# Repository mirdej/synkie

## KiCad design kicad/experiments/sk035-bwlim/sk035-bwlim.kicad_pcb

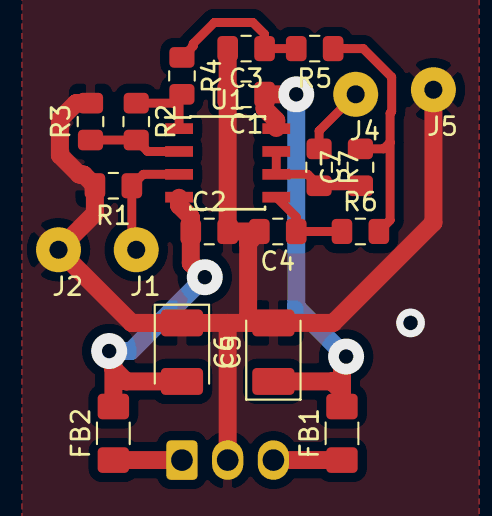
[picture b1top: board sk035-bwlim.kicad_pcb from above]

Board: 2 copper layers, 22 parts (1 on the bottom side), 13 nets.

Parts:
C1, C2: 100n; C_0805_2012Metric_Pad1.15x1.40mm_HandSolder
C3, C7: 47p; C_0805_2012Metric_Pad1.15x1.40mm_HandSolder
C4: 10p; C_0805_2012Metric_Pad1.15x1.40mm_HandSolder
C5, C6: 10u; CP_EIA-3528-21_Kemet-B_Pad1.50x2.35mm_HandSolder
FB1, FB2: Ferrite_Bead; L_1206_3216Metric_Pad1.42x1.75mm_HandSolder
J1, J2, J4, J5: Conn_01x01; Solderpad_1mm
J3: Conn_01x03; Molex_KK-254_AE-6410-03A_1x03_P2.54mm_Vertical
R1: 75; C_0805_2012Metric_Pad1.15x1.40mm_HandSolder
R2, R3: 220; R_0805_2012Metric_Pad1.15x1.40mm_HandSolder
R4, R6: 330; R_0805_2012Metric_Pad1.15x1.40mm_HandSolder
R5: 1k; R_0805_2012Metric_Pad1.15x1.40mm_HandSolder
R7: 75; R_0805_2012Metric_Pad1.15x1.40mm_HandSolder
U1: Opamp_Dual_Generic; SOIC-8_3.9x4.9mm_P1.27mm

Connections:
+5V: C1.1, C5.1, FB1.2, U1.8
-5V: C2.1, C6.2, FB2.2, U1.4
GND: C1.2, C2.2, C3.2, C4.2, C5.2, C6.1, J2.1, J3.2, J5.1, R1.2, R3.2
unnamed: C3.1, R4.1, R5.2
unnamed: C4.1, R6.1, U1.5
unnamed: C7.1, R7.2, U1.6, U1.7
unnamed: C7.2, R5.1, R6.2
unnamed: FB1.1, J3.3
unnamed: FB2.1, J3.1
unnamed: J1.1, R1.1, U1.3
unnamed: J4.1, R7.1
unnamed: R2.1, R4.2, U1.1
unnamed: R2.2, R3.1, U1.2

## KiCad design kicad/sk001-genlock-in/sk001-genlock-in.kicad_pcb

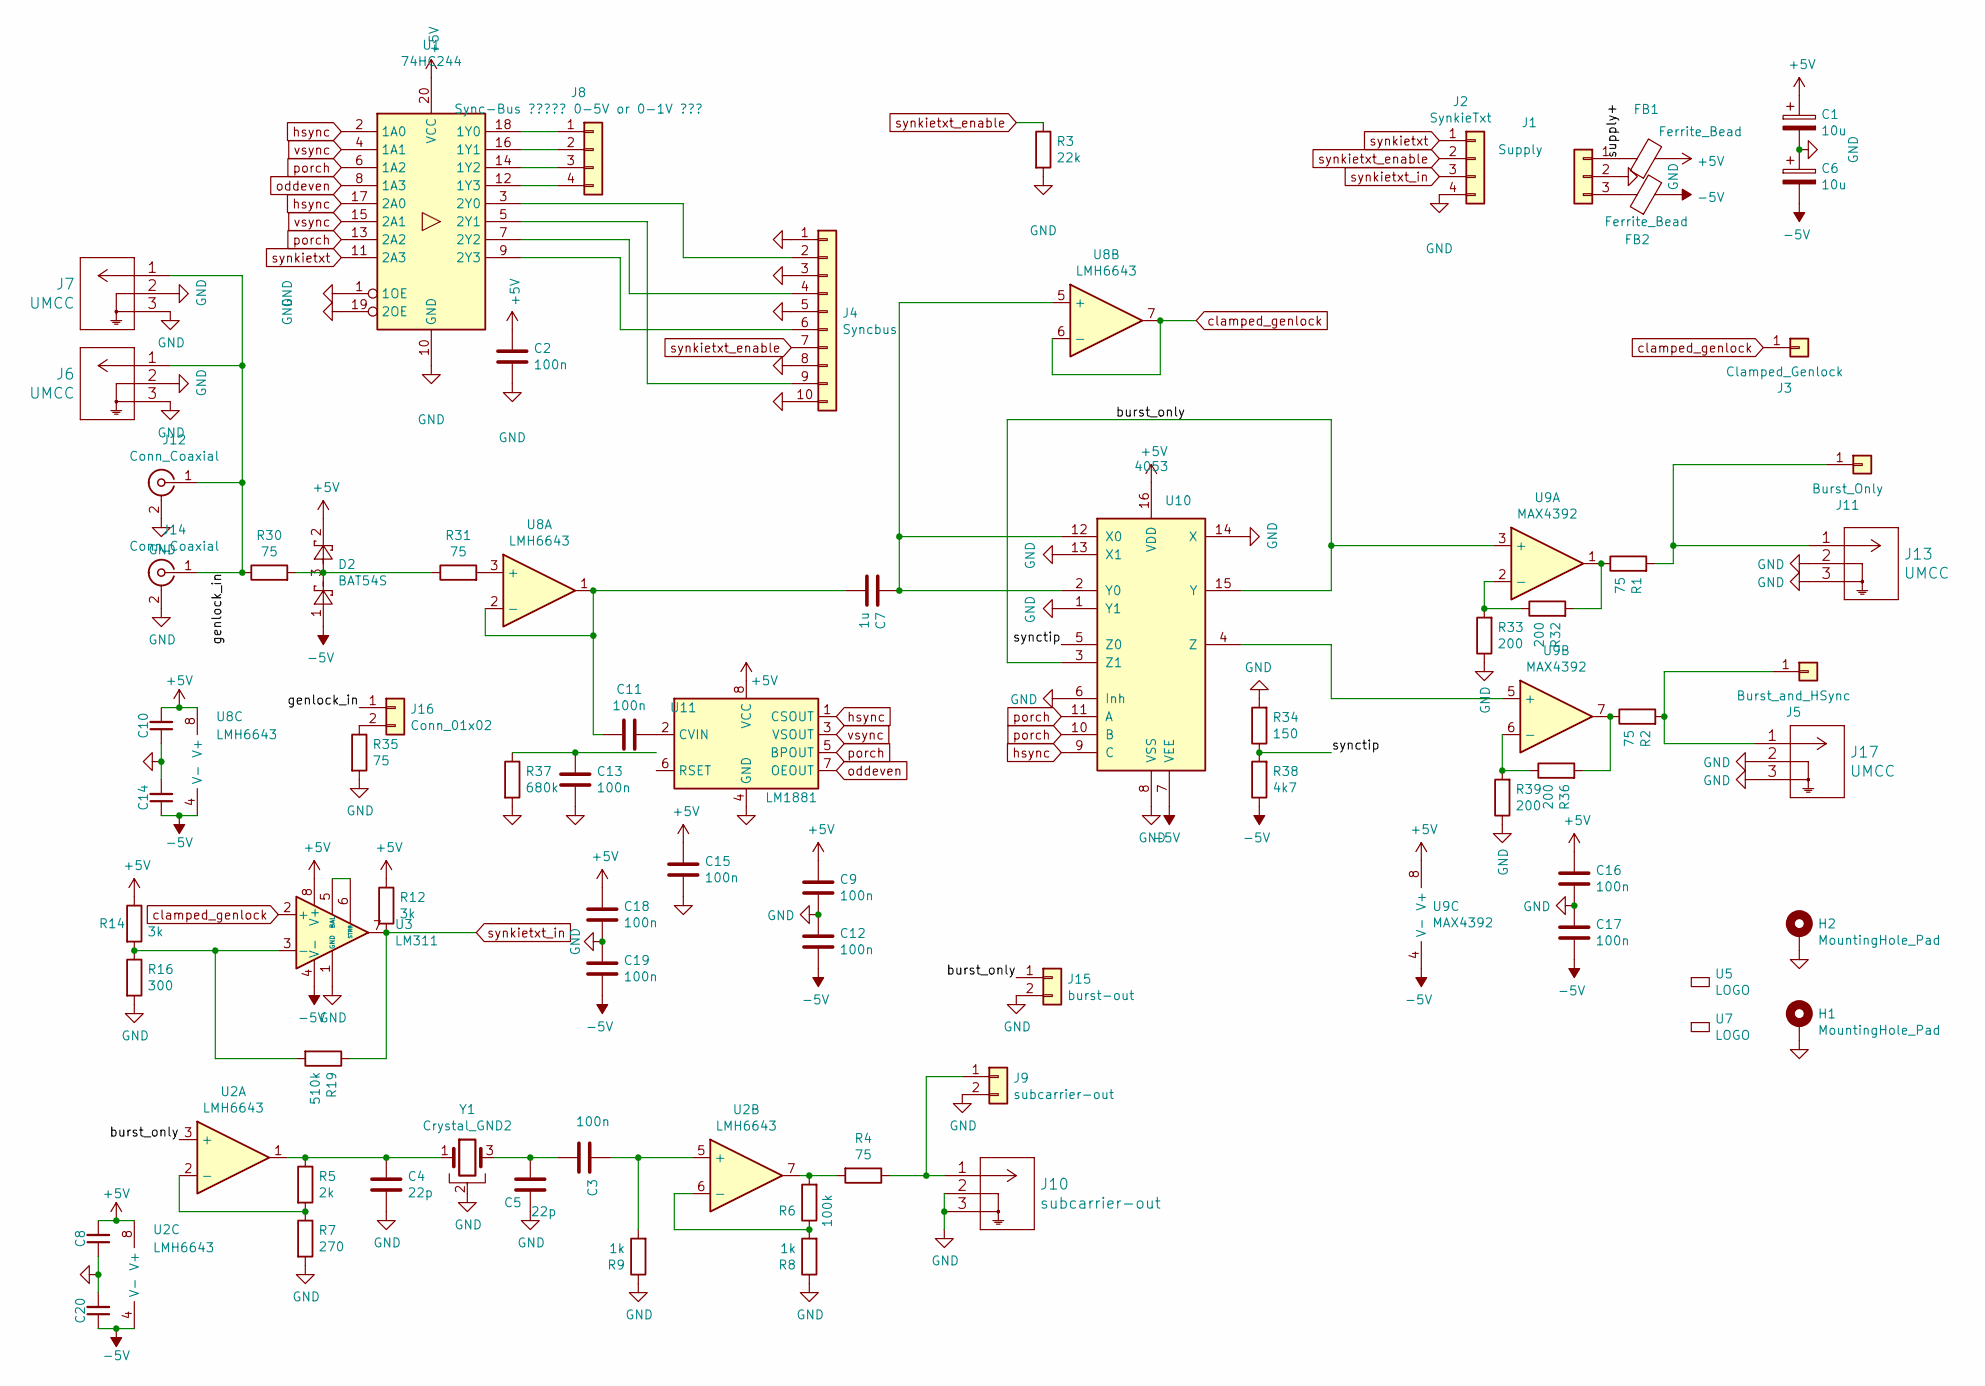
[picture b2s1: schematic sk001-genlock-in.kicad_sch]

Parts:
C1, C6: 10u; CP_EIA-3528-21_Kemet-B_Pad1.50x2.35mm_HandSolder
C2: 100n; R_0603_1608Metric_Pad1.05x0.95mm_HandSolder
C3, C8, C9, C10, C11, C12, C13, C14, C15, C16, C17, C18, C19, C20: 100n; C_0603_1608Metric_Pad1.05x0.95mm_HandSolder
C4, C5: 22p; C_0805_2012Metric_Pad1.15x1.40mm_HandSolder
C7: 1u; C_1206_3216Metric_Pad1.42x1.75mm_HandSolder
D2: BAT54S; SOT-23
FB1, FB2: Ferrite_Bead; L_0805_2012Metric_Pad1.15x1.40mm_HandSolder
H1, H2: MountingHole_Pad; MountingHole_2.7mm_M2.5_ISO7380_Pad
J1: Supply; Molex_KK-254_AE-6410-03A_1x03_P2.54mm_Vertical
J2: SynkieTxt; Molex_KK-254_AE-6410-04A_1x04_P2.54mm_Vertical
J3: Clamped_Genlock; Solderpad_1mm
J4: Syncbus; IDC-Header_2x05_P2.54mm_Vertical
J5: Burst_and_HSync; Solderpad_1mm
J6, J7, J13, J17: UMCC; TE_UMCC_2337019-1
J8: Sync-Bus ????? 0-5V or 0-1V ???; Molex_KK-254_AE-6410-04A_1x04_P2.54mm_Vertical
J9: subcarrier-out; Molex_KK-254_AE-6410-02A_1x02_P2.54mm_Vertical
J10: subcarrier-out; TE_UMCC_2337019-1
J11: Burst_Only; Solderpad_1mm
J12, J14: Conn_Coaxial; BNC_MOLEX_0731000080_Horizontal
J15: burst-out; Molex_KK-254_AE-6410-02A_1x02_P2.54mm_Vertical
J16: Conn_01x02; PinHeader_1x02_P2.54mm_Vertical
R1, R2, R4, R30, R31, R35: 75; R_0805_2012Metric_Pad1.15x1.40mm_HandSolder
R3: 22k; R_0805_2012Metric_Pad1.15x1.40mm_HandSolder
R5: 2k; R_0805_2012Metric_Pad1.15x1.40mm_HandSolder
R6: 100k; R_0805_2012Metric_Pad1.15x1.40mm_HandSolder
R7: 270; R_0805_2012Metric_Pad1.15x1.40mm_HandSolder
R8, R9: 1k; R_0805_2012Metric_Pad1.15x1.40mm_HandSolder
R12, R14: 3k; R_0805_2012Metric_Pad1.15x1.40mm_HandSolder
R16: 300; R_0805_2012Metric_Pad1.15x1.40mm_HandSolder
R19: 510k; R_0805_2012Metric_Pad1.15x1.40mm_HandSolder
R32, R33, R36, R39: 200; R_0805_2012Metric_Pad1.15x1.40mm_HandSolder
R34: 150; R_0805_2012Metric_Pad1.15x1.40mm_HandSolder
R37: 680k; R_0805_2012Metric_Pad1.15x1.40mm_HandSolder
R38: 4k7; R_0805_2012Metric_Pad1.15x1.40mm_HandSolder
U1: 74HC244; SO-20_12.8x7.5mm_P1.27mm
U2, U8: LMH6643; SOIC-8_3.9x4.9mm_P1.27mm
U3: LM311; SOIC-8_3.9x4.9mm_P1.27mm
U5: LOGO; logo_anyma
U7: LOGO; OSHW-Logo2_7.3x6mm_SilkScreen
U9: MAX4392; SOIC-8_3.9x4.9mm_P1.27mm
U10: 4053; SOIC-16_3.9x9.9mm_P1.27mm
U11: LM1881; SOIC-8_3.9x4.9mm_P1.27mm
Y1: Crystal_GND2; Crystal_SMD_HC49-SD_HandSoldering_3pin

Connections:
+5V: C1.1, C2.1, C8.2, C9.1, C10.2, C15.1, C16.1, C18.1, D2.2, FB1.2, R12.1, R14.1, U1.20 (VCC), U2.8 (V+), U3.8 (V+), U8.8 (V+), U9.8 (V+), U10.16 (VDD), U11.8 (VCC)
-5V: C6.2, C12.2, C14.1, C17.2, C19.2, C20.1, D2.1, FB2.2, R38.1, U2.4 (V-), U3.4 (V-), U8.4 (V-), U9.4 (V-), U10.7 (VEE)
/burst_only: J15.1, U2.3 (+), U9.3 (+), U10.3 (Z1), U10.15 (Y)
/genlock_in: J6.1, J7.1, J12.1 (In), J14.1 (In), J16.1, R30.1
/supply+: FB1.1, J1.1
/synctip: R34.1, R38.2, U10.5 (Z0)
GND: C1.2, C2.2, C4.2, C5.2, C6.1, C8.1, C9.2, C10.1, C12.1, C13.2, C14.2, C15.2, C16.2, C17.1, C18.2, C19.1, C20.2, H1.1, H2.1, J1.2, J2.4, J4.1, J4.3, J4.5, J4.8, J4.10, J6.2, J6.3, J7.2, J7.3, J9.2, J10.2, J10.3, J12.2 (Ext), J13.2, J13.3, J14.2 (Ext), J15.2, J17.2, J17.3, R3.2, R7.2, R8.1, R9.1, R16.2, R33.1, R34.2, R35.2, R37.2, R39.1, U1.1 (1OE), U1.10 (GND), U1.19 (2OE), U3.1 (GND), U10.1 (Y1), U10.6 (Inh), U10.8 (VSS), U10.13 (X1), U10.14 (X), U11.4 (GND), Y1.2
unnamed: C3.1, R9.2, U2.5 (+)
unnamed: C3.2, C5.1, Y1.3
unnamed: C4.1, R5.1, U2.1, Y1.1
unnamed: C7.1, U8.5 (+), U10.2 (Y0), U10.12 (X0)
unnamed: C11.1, U11.2 (CVIN)
unnamed: C7.2, C11.2, U8.1, U8.2 (-)
unnamed: D2.3, R30.2, R31.1
unnamed: FB2.1, J1.3
unnamed: J4.2, U1.3 (2Y0)
unnamed: J4.4, U1.7 (2Y2)
unnamed: J4.6, U1.9 (2Y3)
unnamed: J4.9, U1.5 (2Y1)
unnamed: J8.1, U1.18 (1Y0)
unnamed: J8.2, U1.16 (1Y1)
unnamed: J8.3, U1.14 (1Y2)
unnamed: J8.4, U1.12 (1Y3)
unnamed: J9.1, J10.1, R4.1
unnamed: J11.1, J13.1, R1.2
unnamed: J16.2, R35.1
unnamed: J5.1, J17.1, R2.2
unnamed: R1.1, R32.2, U9.1
unnamed: R2.1, R36.2, U9.7
unnamed: R4.2, R6.2, U2.7
unnamed: R5.2, R7.1, U2.2 (-)
unnamed: R6.1, R8.2, U2.6 (-)
unnamed: R14.2, R16.1, R19.2, U3.3 (-)
unnamed: R31.2, U8.3 (+)
unnamed: R32.1, R33.2, U9.2 (-)
unnamed: R36.1, R39.2, U9.6 (-)
unnamed: U3.5 (BAL), U3.6 (STRB)
unnamed: U9.5 (+), U10.4 (Z)
clamped_genlock: J3.1, U3.2 (+), U8.6 (-), U8.7
hsync: U1.2 (1A0), U1.17 (2A0), U10.9 (C), U11.1 (CSOUT)
oddeven: U1.8 (1A3), U11.7 (OEOUT)
porch: U1.6 (1A2), U1.13 (2A2), U10.10 (B), U10.11 (A), U11.5 (BPOUT)
synkietxt: J2.1, U1.11 (2A3)
synkietxt_enable: J2.2, J4.7, R3.1
synkietxt_in: J2.3, R12.2, R19.1, U3.7
vsync: U1.4 (1A1), U1.15 (2A1), U11.3 (VSOUT)

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
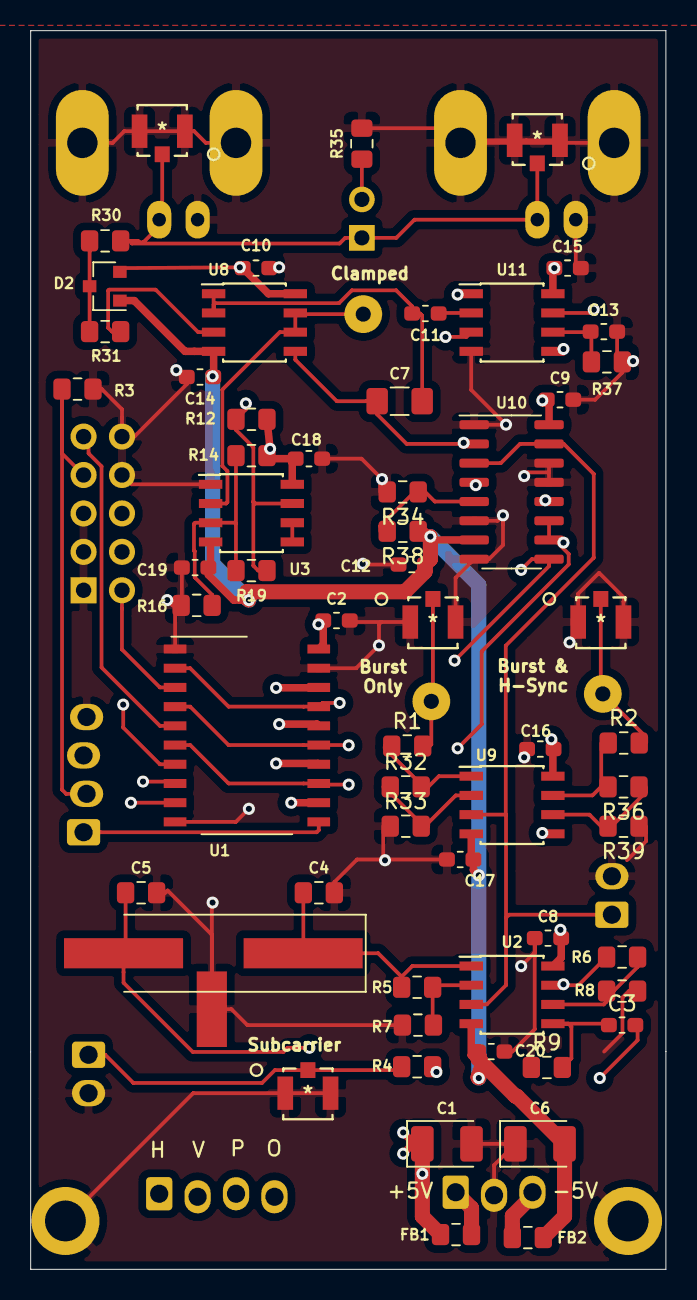
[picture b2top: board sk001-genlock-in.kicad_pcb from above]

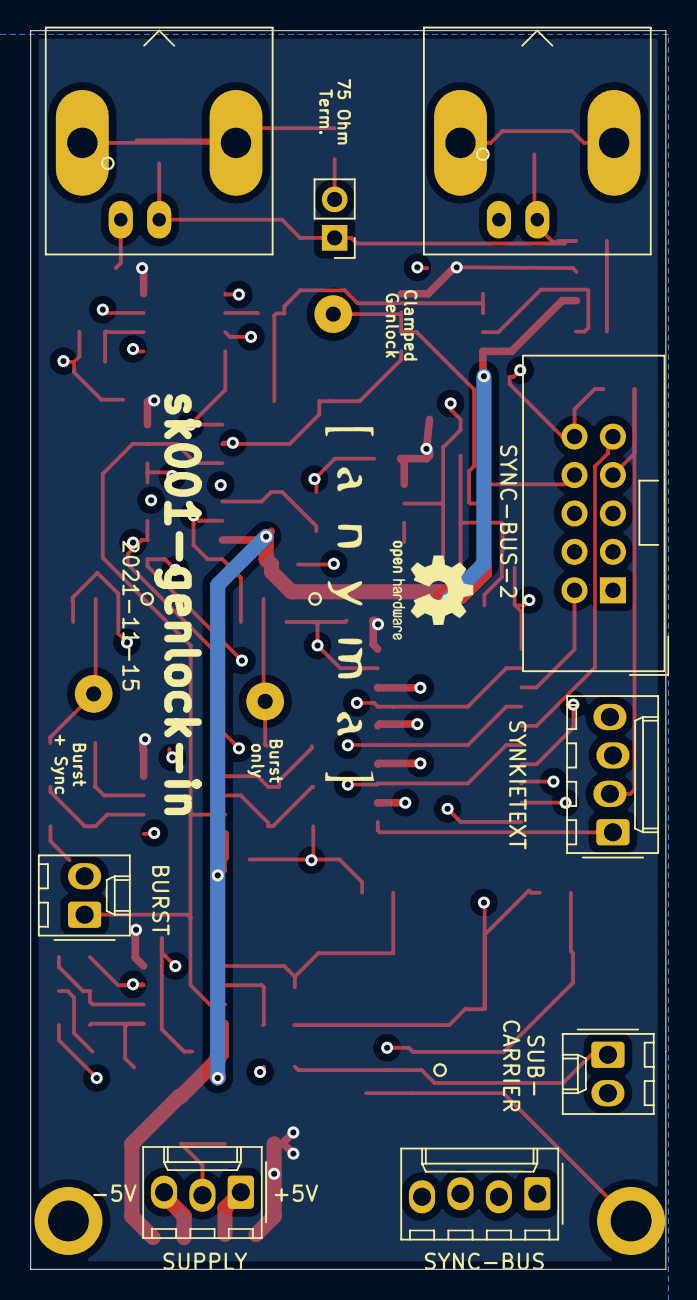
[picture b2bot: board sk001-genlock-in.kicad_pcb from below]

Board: 4 copper layers, 42.0 x 81.9 mm, 75 parts (11 on the bottom side), 47 nets.

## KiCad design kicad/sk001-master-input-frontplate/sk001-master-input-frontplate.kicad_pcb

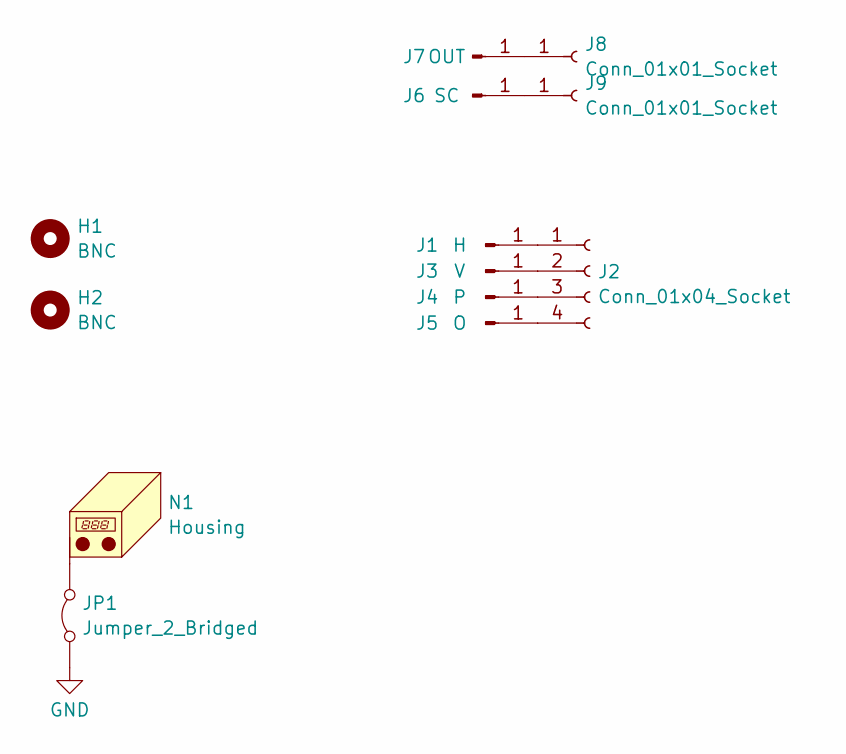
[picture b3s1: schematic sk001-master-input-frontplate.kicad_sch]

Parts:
H1, H2: BNC; MolexBNCFrontpanel
J1: H; Banana2mm-Löthülse
J2: Conn_01x04_Socket; smd-4pin
J3: V; Banana2mm-Löthülse
J4: P; Banana2mm-Löthülse
J5: O; Banana2mm-Löthülse
J6: SC; Banana2mm-Löthülse
J7: OUT; Banana2mm-Löthülse
J8, J9: Conn_01x01_Socket; smd-1pin
JP1: Jumper_2_Bridged; SolderJumper-2_P1.3mm_Bridged2Bar_Pad1.0x1.5mm
N1: Housing; Frontplate_20mm

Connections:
GND: JP1.1 (A)
unnamed: J1.1, J2.1
unnamed: J2.2, J3.1
unnamed: J2.3, J4.1
unnamed: J2.4, J5.1
unnamed: J6.1, J9.1
unnamed: J7.1, J8.1
unnamed: JP1.2 (B), N1.1 (PAD)

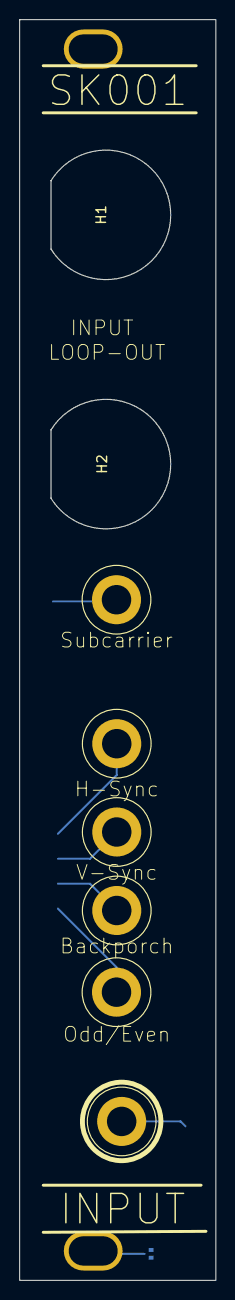
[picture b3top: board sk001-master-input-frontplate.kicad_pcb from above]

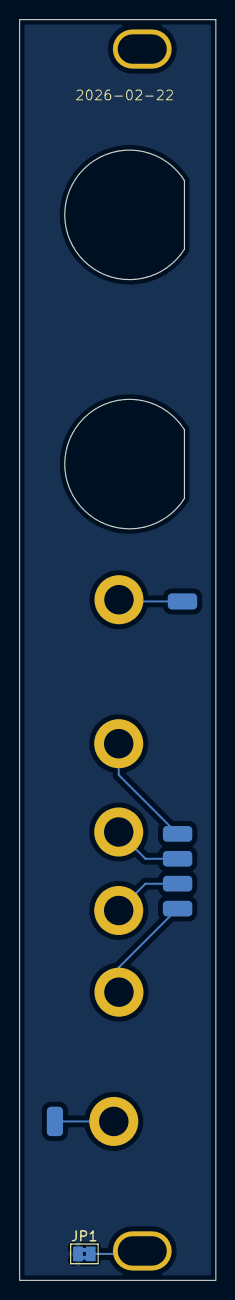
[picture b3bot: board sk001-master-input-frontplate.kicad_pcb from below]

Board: 2 copper layers, 20.0 x 128.5 mm, 13 parts (4 on the bottom side), 7 nets.

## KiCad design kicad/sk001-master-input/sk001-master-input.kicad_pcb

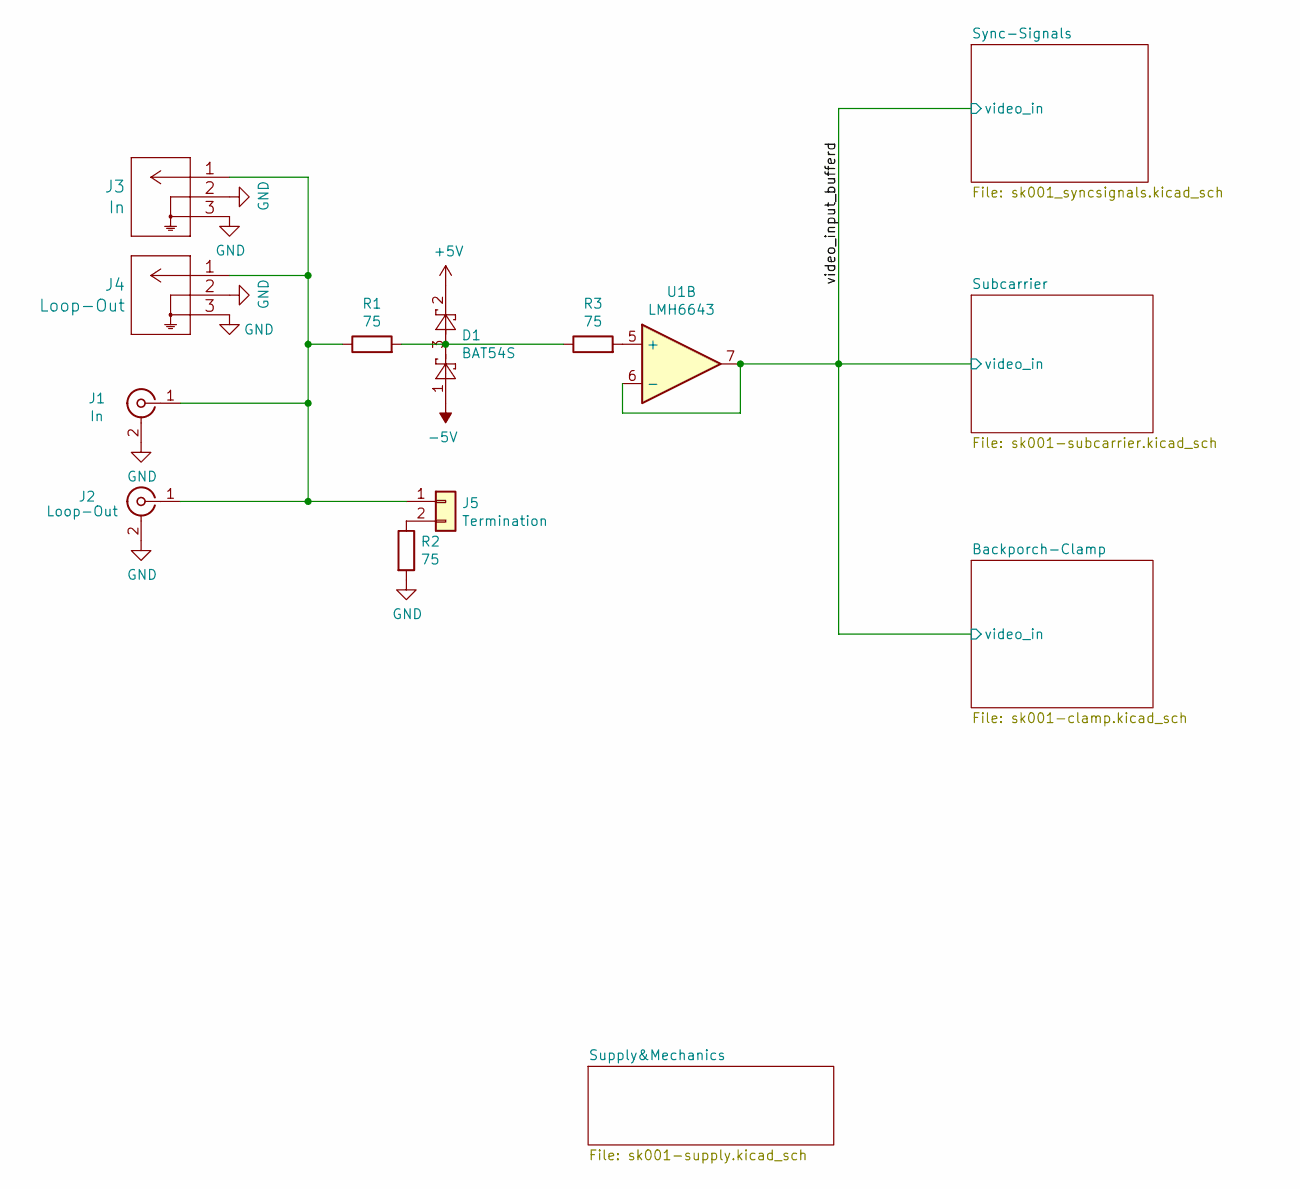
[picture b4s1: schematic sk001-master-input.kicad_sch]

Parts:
D1: BAT54S; SOT-23
J1: In; BNC_MOLEX_0731000080_Horizontal
J2: Loop-Out; BNC_MOLEX_0731000080_Horizontal
J3: In; TE_UMCC_2337019-1
J4: Loop-Out; TE_UMCC_2337019-1
J5: Termination; PinHeader_1x02_P2.54mm_Vertical
R1, R2, R3: 75; R_0805_2012Metric
U1: LMH6643; SOIC-8_3.9x4.9mm_P1.27mm

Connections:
+5V: D1.2; also elsewhere on the board
-5V: D1.1; also elsewhere on the board
/video_input_bufferd: U1.6 (-), U1.7; also elsewhere on the board
GND: J1.2 (Ext), J2.2 (Ext), J3.2, J3.3, J4.2, J4.3, R2.2; also elsewhere on the board
unnamed: D1.3, R1.2, R3.1
unnamed: J1.1 (In), J2.1 (In), J3.1, J4.1, J5.1, R1.1
unnamed: J5.2, R2.1
unnamed: R3.2, U1.5 (+)

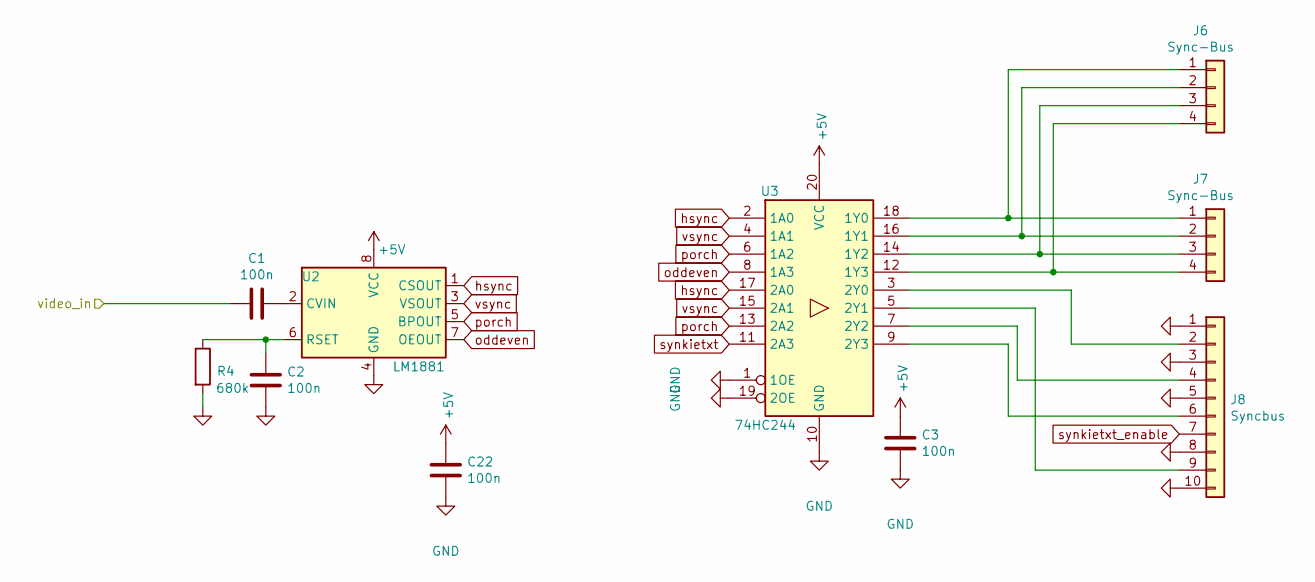
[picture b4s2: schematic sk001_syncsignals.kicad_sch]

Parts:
C1, C2, C3, C22: 100n; C_0603_1608Metric
J6, J7: Sync-Bus; Molex_KK-254_AE-6410-04A_1x04_P2.54mm_Vertical
J8: Syncbus; IDC-Header_2x05_P2.54mm_Vertical
R4: 680k; R_0805_2012Metric
U2: LM1881; SOIC-8_3.9x4.9mm_P1.27mm
U3: 74HC244; SO-20_12.8x7.5mm_P1.27mm

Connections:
+5V: C3.1, C22.1, U2.8 (VCC), U3.20 (VCC); also elsewhere on the board
/video_input_bufferd: C1.2; also elsewhere on the board
GND: C2.2, C3.2, C22.2, J8.1, J8.3, J8.5, J8.8, J8.10, R4.2, U2.4 (GND), U3.1 (1OE), U3.10 (GND), U3.19 (2OE); also elsewhere on the board
unnamed: J6.1, J7.1, U3.18 (1Y0)
unnamed: J6.2, J7.2, U3.16 (1Y1)
unnamed: J6.3, J7.3, U3.14 (1Y2)
unnamed: J6.4, J7.4, U3.12 (1Y3)
unnamed: J8.2, U3.3 (2Y0)
unnamed: J8.4, U3.7 (2Y2)
unnamed: J8.6, U3.9 (2Y3)
unnamed: J8.9, U3.5 (2Y1)
unnamed: C1.1, U2.2 (CVIN)
unnamed: C2.1, R4.1, U2.6 (RSET)
hsync: U2.1 (CSOUT), U3.2 (1A0), U3.17 (2A0); also elsewhere on the board
oddeven: U2.7 (OEOUT), U3.8 (1A3)
porch: U2.5 (BPOUT), U3.6 (1A2), U3.13 (2A2); also elsewhere on the board
synkietxt: U3.11 (2A3)
synkietxt_enable: J8.7
vsync: U2.3 (VSOUT), U3.4 (1A1), U3.15 (2A1)

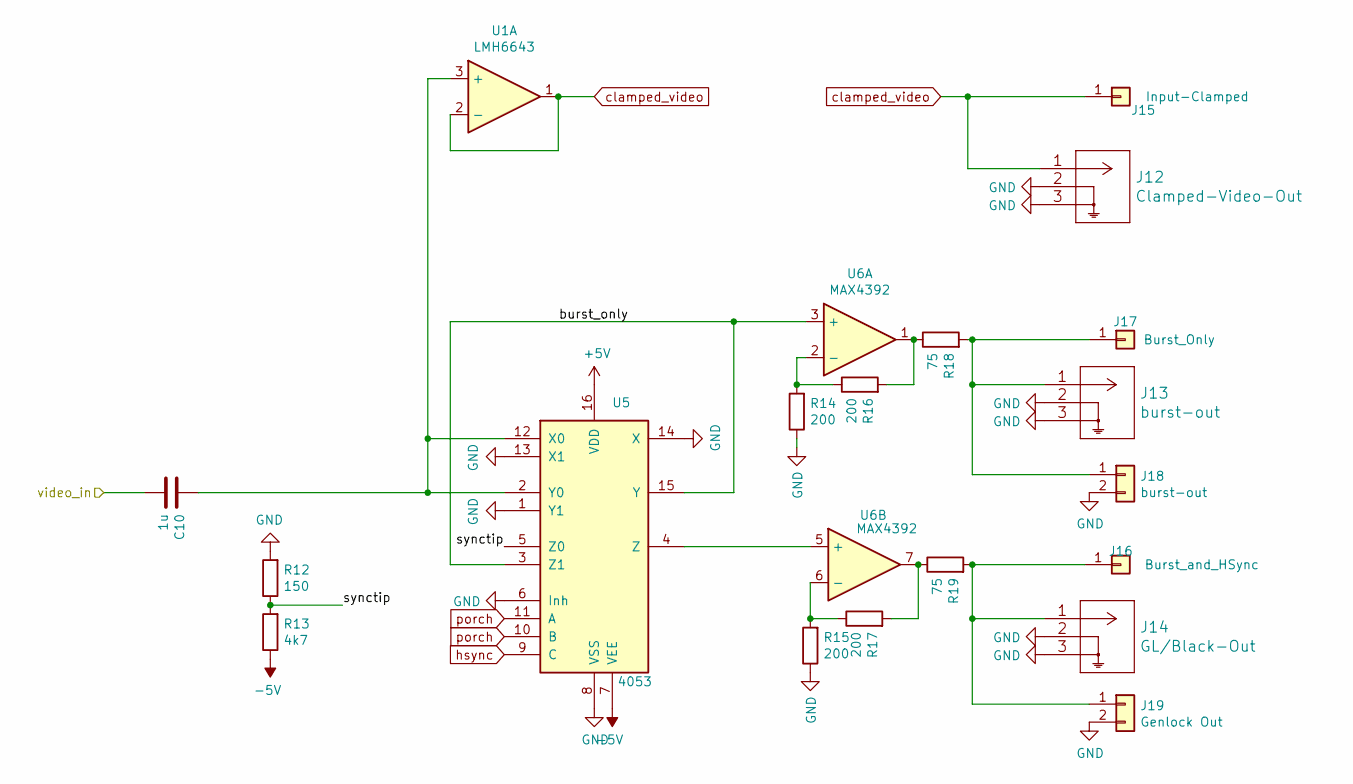
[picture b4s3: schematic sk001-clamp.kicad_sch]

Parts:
C10: 1u; C_0603_1608Metric
J12: Clamped-Video-Out; TE_UMCC_2337019-1
J13: burst-out; TE_UMCC_2337019-1
J14: GL/Black-Out; TE_UMCC_2337019-1
J15: Input-Clamped; TestPoint_THTPad_D4.0mm_Drill2.0mm
J16: Burst_and_HSync; TestPoint_THTPad_D4.0mm_Drill2.0mm
J17: Burst_Only; TestPoint_THTPad_D4.0mm_Drill2.0mm
J18: burst-out; Molex_KK-254_AE-6410-02A_1x02_P2.54mm_Vertical
J19: Genlock Out; Molex_KK-254_AE-6410-02A_1x02_P2.54mm_Vertical
R12: 150; R_0805_2012Metric
R13: 4k7; R_0805_2012Metric
R14, R15, R16, R17: 200; R_0805_2012Metric
R18, R19: 75; R_0805_2012Metric
U1: LMH6643; SOIC-8_3.9x4.9mm_P1.27mm
U5: 4053; SOIC-16_3.9x9.9mm_P1.27mm
U6: MAX4392; SOIC-8_3.9x4.9mm_P1.27mm

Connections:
+5V: U5.16 (VDD); also elsewhere on the board
-5V: R13.1, U5.7 (VEE); also elsewhere on the board
/Backporch-Clamp/burst_only: U5.3 (Z1), U5.15 (Y), U6.3 (+)
/Backporch-Clamp/synctip: R12.1, R13.2, U5.5 (Z0)
/video_input_bufferd: C10.2; also elsewhere on the board
GND: J12.2, J12.3, J13.2, J13.3, J14.2, J14.3, J18.2, J19.2, R12.2, R14.1, R15.1, U5.1 (Y1), U5.6 (Inh), U5.8 (VSS), U5.13 (X1), U5.14 (X); also elsewhere on the board
unnamed: J14.1, J16.1, J19.1, R19.2
unnamed: J13.1, J17.1, J18.1, R18.2
unnamed: R16.2, R18.1, U6.1
unnamed: R17.2, R19.1, U6.7
unnamed: C10.1, U1.3 (+), U5.2 (Y0), U5.12 (X0)
unnamed: U5.4 (Z), U6.5 (+)
unnamed: R14.2, R16.1, U6.2 (-)
unnamed: R15.2, R17.1, U6.6 (-)
clamped_video: J12.1, J15.1, U1.1, U1.2 (-)
hsync: U5.9 (C); also elsewhere on the board
porch: U5.10 (B), U5.11 (A); also elsewhere on the board

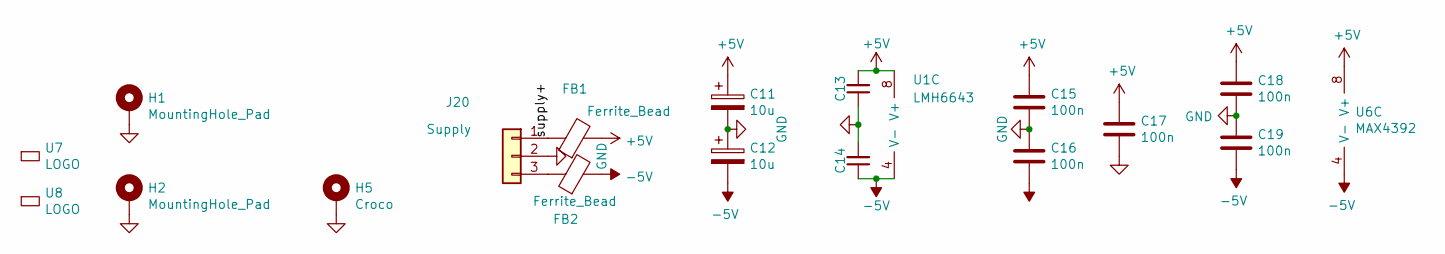
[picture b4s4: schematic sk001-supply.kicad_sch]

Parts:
C11, C12: 10u; C_0805_2012Metric
C13, C14, C15, C16, C17, C18, C19: 100n; C_0603_1608Metric
FB1, FB2: Ferrite_Bead; L_0805_2012Metric_Pad1.15x1.40mm_HandSolder
H1, H2: MountingHole_Pad; MountingHole_2.7mm_M2.5_ISO7380_Pad
H5: Croco; CrocodileGroundPad
J20: Supply; Molex_KK-254_AE-6410-03A_1x03_P2.54mm_Vertical
U1: LMH6643; SOIC-8_3.9x4.9mm_P1.27mm
U6: MAX4392; SOIC-8_3.9x4.9mm_P1.27mm
U7: LOGO; logo_anyma
U8: LOGO; OSHW-Logo2_7.3x6mm_SilkScreen

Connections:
+5V: C11.1, C13.2, C15.1, C17.1, C18.1, FB1.2, U1.8 (V+), U6.8 (V+); also elsewhere on the board
-5V: C12.2, C14.1, C16.2, C19.2, FB2.2, U1.4 (V-), U6.4 (V-); also elsewhere on the board
/Supply&Mechanics/supply+: FB1.1, J20.1
GND: C11.2, C12.1, C13.1, C14.2, C15.2, C16.1, C17.2, C18.2, C19.1, H1.1, H2.1, H5.1, J20.2; also elsewhere on the board
unnamed: FB2.1, J20.3

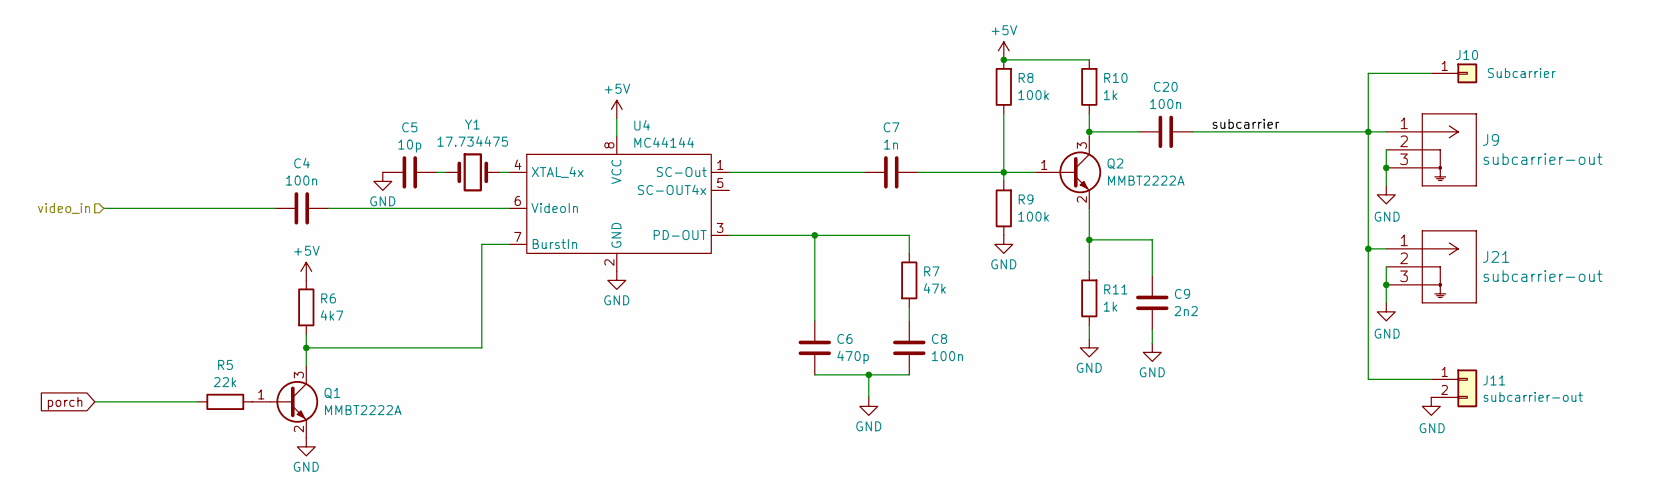
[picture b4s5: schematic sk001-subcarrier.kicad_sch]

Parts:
C4, C8: 100n; C_0603_1608Metric
C5: 10p; C_0805_2012Metric
C6: 470p; C_0805_2012Metric
C7: 1n; C_0805_2012Metric
C9: 2n2; C_0805_2012Metric
C20: 100n; C_0805_2012Metric
J9, J21: subcarrier-out; TE_UMCC_2337019-1
J10: Subcarrier; TestPoint_THTPad_D4.0mm_Drill2.0mm
J11: subcarrier-out; Molex_KK-254_AE-6410-02A_1x02_P2.54mm_Vertical
Q1, Q2: MMBT2222A; SOT-23
R5: 22k; R_0805_2012Metric
R6: 4k7; R_0805_2012Metric
R7: 47k; R_0805_2012Metric
R8, R9: 100k; R_0805_2012Metric
R10, R11: 1k; R_0805_2012Metric
U4: MC44144; SOIC-8_3.9x4.9mm_P1.27mm
Y1: 17.734475; Crystal_SMD_HC49-SD

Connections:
+5V: R6.1, R8.2, R10.2, U4.8 (VCC); also elsewhere on the board
/Subcarrier/subcarrier: C20.2, J9.1, J10.1, J11.1, J21.1
/video_input_bufferd: C4.1; also elsewhere on the board
GND: C5.1, C6.2, C8.2, C9.2, J9.2, J9.3, J11.2, J21.2, J21.3, Q1.2 (E), R9.1, R11.1, U4.2 (GND); also elsewhere on the board
unnamed: C5.2, Y1.1
unnamed: C8.1, R7.2
unnamed: Q1.1 (B), R5.2
unnamed: Q1.3 (C), R6.2, U4.7 (BurstIn)
unnamed: C7.2, Q2.1 (B), R8.1, R9.2
unnamed: C20.1, Q2.3 (C), R10.1
unnamed: C9.1, Q2.2 (E), R11.2
unnamed: C6.1, R7.1, U4.3 (PD-OUT)
unnamed: C7.1, U4.1 (SC-Out)
unnamed: C4.2, U4.6 (VideoIn)
unnamed: U4.4 (XTAL_4x), Y1.2
porch: R5.1; also elsewhere on the board

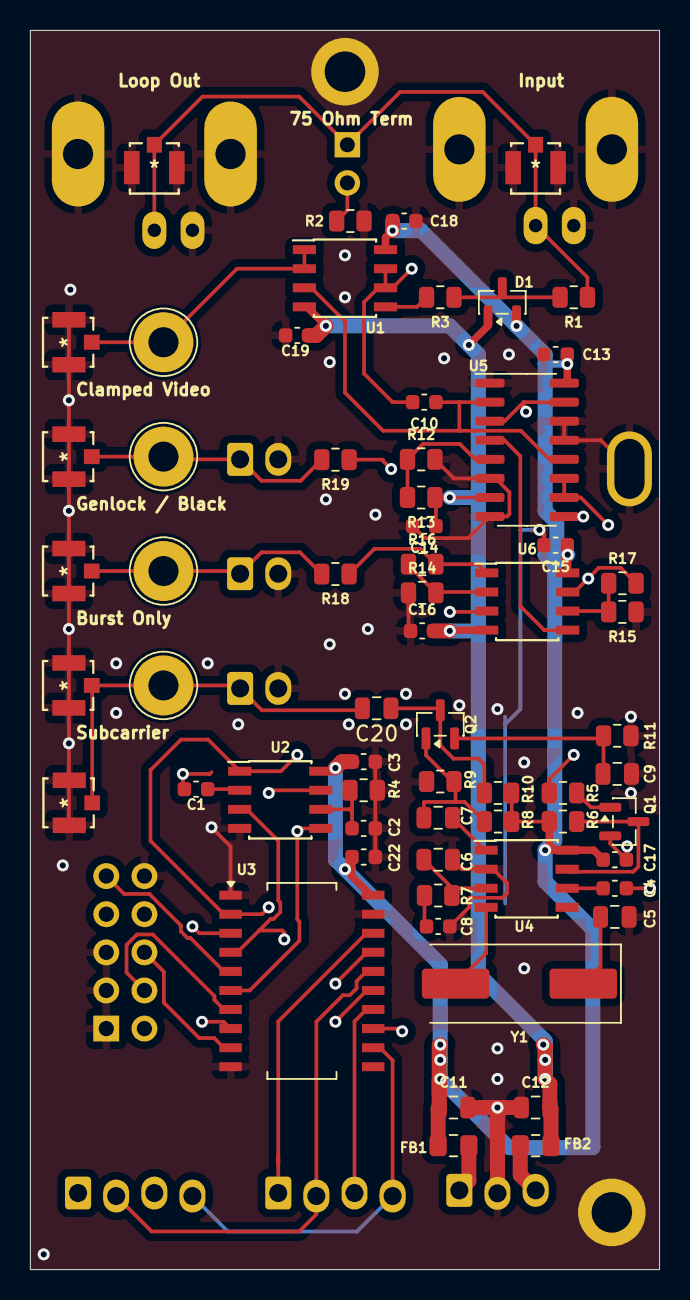
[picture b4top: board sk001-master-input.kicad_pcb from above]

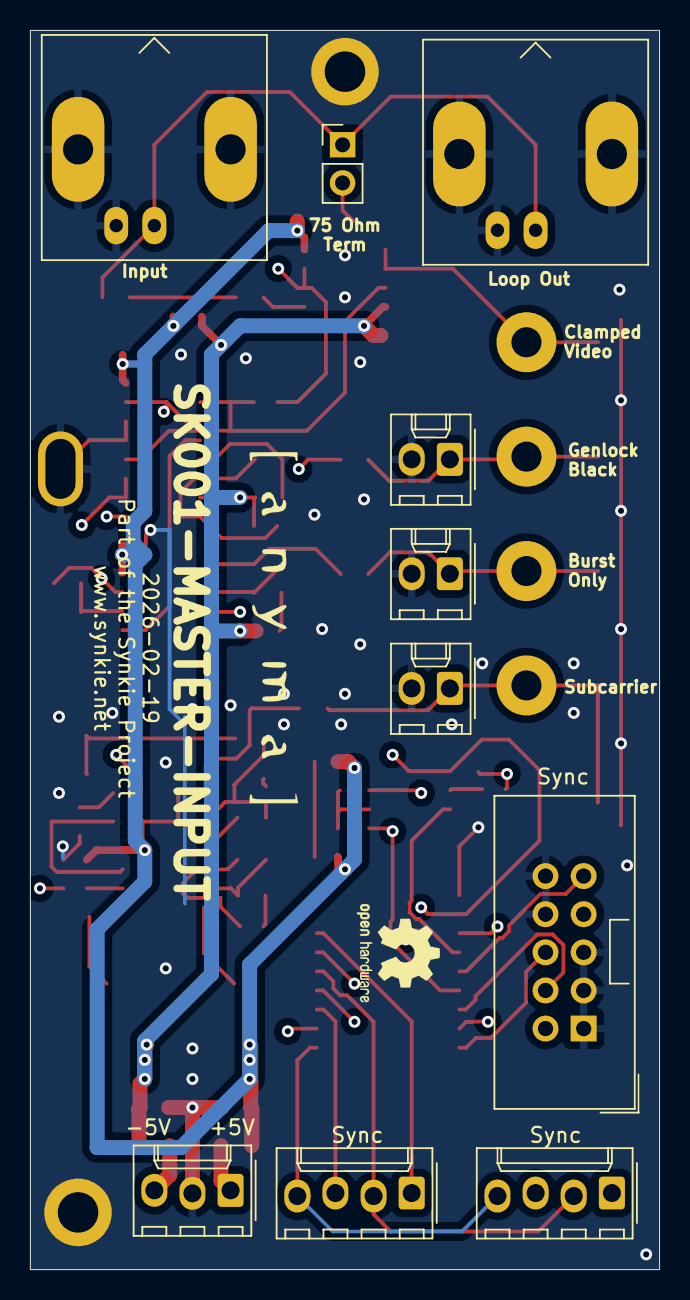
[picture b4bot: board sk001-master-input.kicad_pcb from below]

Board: 4 copper layers, 41.9 x 82.5 mm, 78 parts (12 on the bottom side), 47 nets.

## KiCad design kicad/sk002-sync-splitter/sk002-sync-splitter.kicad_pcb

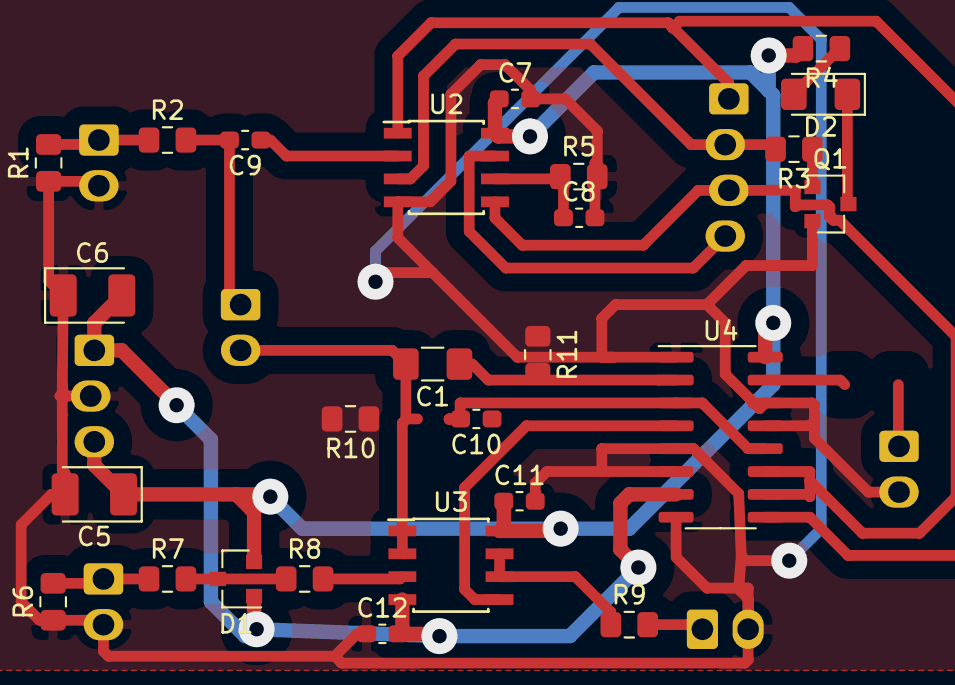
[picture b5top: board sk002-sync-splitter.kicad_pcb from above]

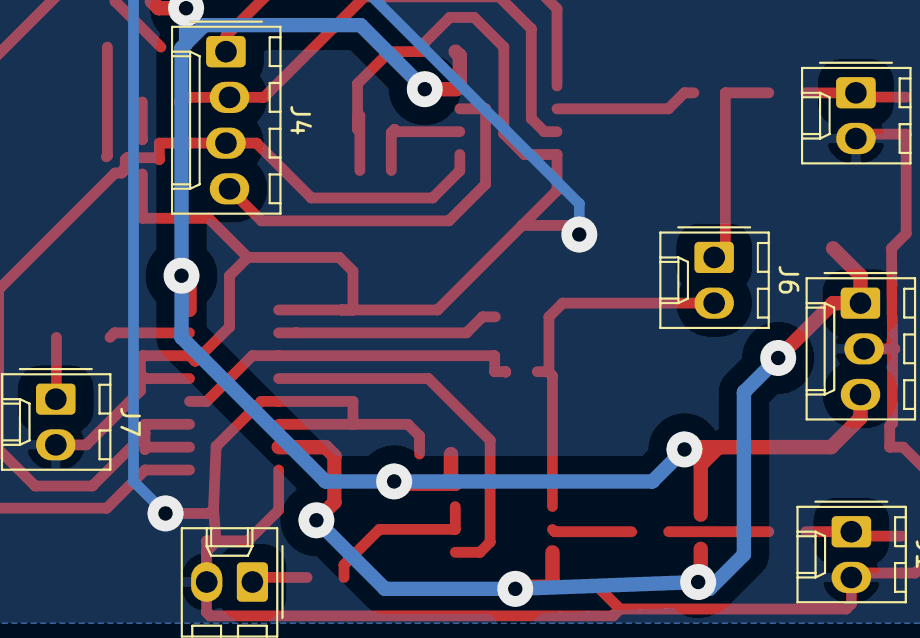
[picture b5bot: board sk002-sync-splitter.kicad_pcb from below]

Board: 2 copper layers, 33 parts (7 on the bottom side), 25 nets.

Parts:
C1: 68p; C_1206_3216Metric_Pad1.42x1.75mm_HandSolder
C5, C6: 10u; CP_EIA-3528-21_Kemet-B_Pad1.50x2.35mm_HandSolder
C7, C8, C9, C10, C11, C12: 100n; C_0603_1608Metric_Pad1.05x0.95mm_HandSolder
D1: BAT54S; SOT-23
D2: LED; LED_1206_3216Metric_Pad1.42x1.75mm_HandSolder
J1: INPUT; Molex_KK-254_AE-6410-02A_1x02_P2.54mm_Vertical
J2: INPUT_CLAMPED; Molex_KK-254_AE-6410-02A_1x02_P2.54mm_Vertical
J3: GENLOCK_IN; Molex_KK-254_AE-6410-02A_1x02_P2.54mm_Vertical
J4: Conn_01x04; Molex_KK-254_AE-6410-04A_1x04_P2.54mm_Vertical
J5: Conn_01x03; Molex_KK-254_AE-6410-03A_1x03_P2.54mm_Vertical
J6: Conn_01x02; Molex_KK-254_AE-6410-02A_1x02_P2.54mm_Vertical
J7: BURSTOUT; Molex_KK-254_AE-6410-02A_1x02_P2.54mm_Vertical
Q1: BC847; SOT-23
R1: 47k; R_0805_2012Metric_Pad1.15x1.40mm_HandSolder
R2, R6, R7, R8, R9, R10: 75; R_0805_2012Metric_Pad1.15x1.40mm_HandSolder
R3: 300; R_0805_2012Metric_Pad1.15x1.40mm_HandSolder
R4, R11: 560; R_0805_2012Metric_Pad1.15x1.40mm_HandSolder
R5: 680k; R_0805_2012Metric_Pad1.15x1.40mm_HandSolder
U2: LM1881; SOIC-8_3.9x4.9mm_P1.27mm
U3: LMH6643; SOIC-8_3.9x4.9mm_P1.27mm
U4: 4053; SOIC-16_3.9x9.9mm_P1.27mm

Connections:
+5V: C5.1, C7.1, C11.1, D1.2, J5.3, R4.2, U2.8, U3.8, U4.16
-5V: C6.2, C12.2, D1.1, J5.1, U3.4, U4.7
/clamp: C10.1, U4.3, U4.12
/colorburst: J7.1, U4.15
/hsync: J4.1, U2.1, U4.9
/oe: J4.4, U2.7
/porch: J4.3, U2.5, U4.10, U4.11
/vsync: J4.2, R3.2, U2.3
GND: C5.2, C6.1, C7.2, C8.2, C11.2, C12.1, J1.2, J2.2, J3.2, J5.2, J7.2, Q1.2, R1.1, R5.2, R6.1, R11.1, U2.4, U4.1, U4.5, U4.6, U4.8, U4.13, U4.14
unnamed: C1.1, R11.2, U4.2
unnamed: C1.2, J6.2, R10.2, U3.1, U3.2
unnamed: C8.1, R5.1, U2.6
unnamed: C9.1, U2.2
unnamed: C9.2, J6.1, R2.2
unnamed: C10.2, R10.1
unnamed: D1.3, R7.2, R8.1
unnamed: D2.1, Q1.3
unnamed: D2.2, R4.1
unnamed: J1.1, R6.2, R7.1
unnamed: J2.1, R9.2
unnamed: J3.1, R1.2, R2.1
unnamed: Q1.1, R3.1
unnamed: R8.2, U3.3
unnamed: R9.1, U3.6, U3.7
unnamed: U3.5, U4.4

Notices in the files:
parts and their libraries:
Copyright 2016 Accelerated Designs. All rights reserved.
